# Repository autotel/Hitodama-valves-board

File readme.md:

# to fix:
* ---Teensy-board, connect VCC to teensy 3v---
* ---caps wrong way around in valves boards.---
* ---check about the twistedness of the ribbon cable---

* Cannot use the DAC pins (A21,A22) as digital!

board to control two valves and two pressure sensors from microcontroller.

Electronic design: Avner Peled & Joaquín Aldunate

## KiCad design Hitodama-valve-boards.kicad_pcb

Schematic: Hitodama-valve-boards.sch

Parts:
C1, C2: 100uF 25v; CP_Radial_D8.0mm_P3.80mm
D1, D2: D; D_5W_P12.70mm_Horizontal
H1, H2, H3, H4: MountingHole; MountingHole_3.2mm_M3
J1: Solenoid A; TerminalBlock_Altech_AK300-2_P5.00mm
J2: Solenoid B; TerminalBlock_Altech_AK300-2_P5.00mm
JP1, JP2: (A,B)IN 1; PinHeader_1x02_P2.54mm_Vertical
R1, R5: 80K; R_Axial_DIN0309_L9.0mm_D3.2mm_P12.70mm_Horizontal
R2, R6: 10K; R_Axial_DIN0309_L9.0mm_D3.2mm_P12.70mm_Horizontal
R3, R7: 3.3K; R_Axial_DIN0309_L9.0mm_D3.2mm_P12.70mm_Horizontal
R4, R8: 33K; R_Axial_DIN0309_L9.0mm_D3.2mm_P12.70mm_Horizontal
U1: LM358; DIP-8_W7.62mm_Socket_LongPads
U2: Pressure_b; DIP-6_W10.16mm
U3: Pressure_a; DIP-6_W10.16mm
U4: ChamberBoard_Holder; chamber_board_holder_ 5-5530843-3_male
U5: Pololu-713; pololu713

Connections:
+12V: U4.7, U5.7
/A.IN.1: JP1.1, U4.3, U5.14
/A.IN.2: U4.4, U5.15
/A.PRESSURE: R8.1, U1.1, U4.10
/A.PWM: JP2.2, U4.1, U5.16
/B.IN.1: JP1.2, U4.5, U5.12
/B.IN.2: U4.6, U5.11
/B.PRESSURE: R4.1, U1.7, U4.11
/B.PWM: JP2.1, U4.2, U5.10
/HVA+: D1.1 (K), J1.2, U5.3
/HVA-: D1.2 (A), J1.1, U5.4
/HVB+: D2.1 (K), J2.2, U5.6
/HVB-: D2.2 (A), J2.1, U5.5
/stby: U4.12, U5.13
GND: C1.2, C2.2, R1.1, R5.1, U1.4 (V-), U2.2, U3.2, U4.8, U5.1, U5.9
unnamed: R1.2, R2.2, U1.5 (+)
unnamed: R2.1, U2.4
unnamed: R3.1, R4.2, U1.6 (-)
unnamed: R3.2, U2.1, U2.6
unnamed: R5.2, R6.2, U1.3 (+)
unnamed: R6.1, U3.4
unnamed: R7.1, R8.2, U1.2 (-)
unnamed: R7.2, U3.1, U3.6
VCC: C1.1, C2.1, U1.8 (V+), U2.5, U3.5, U4.9, U5.2

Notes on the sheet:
Modular
Head

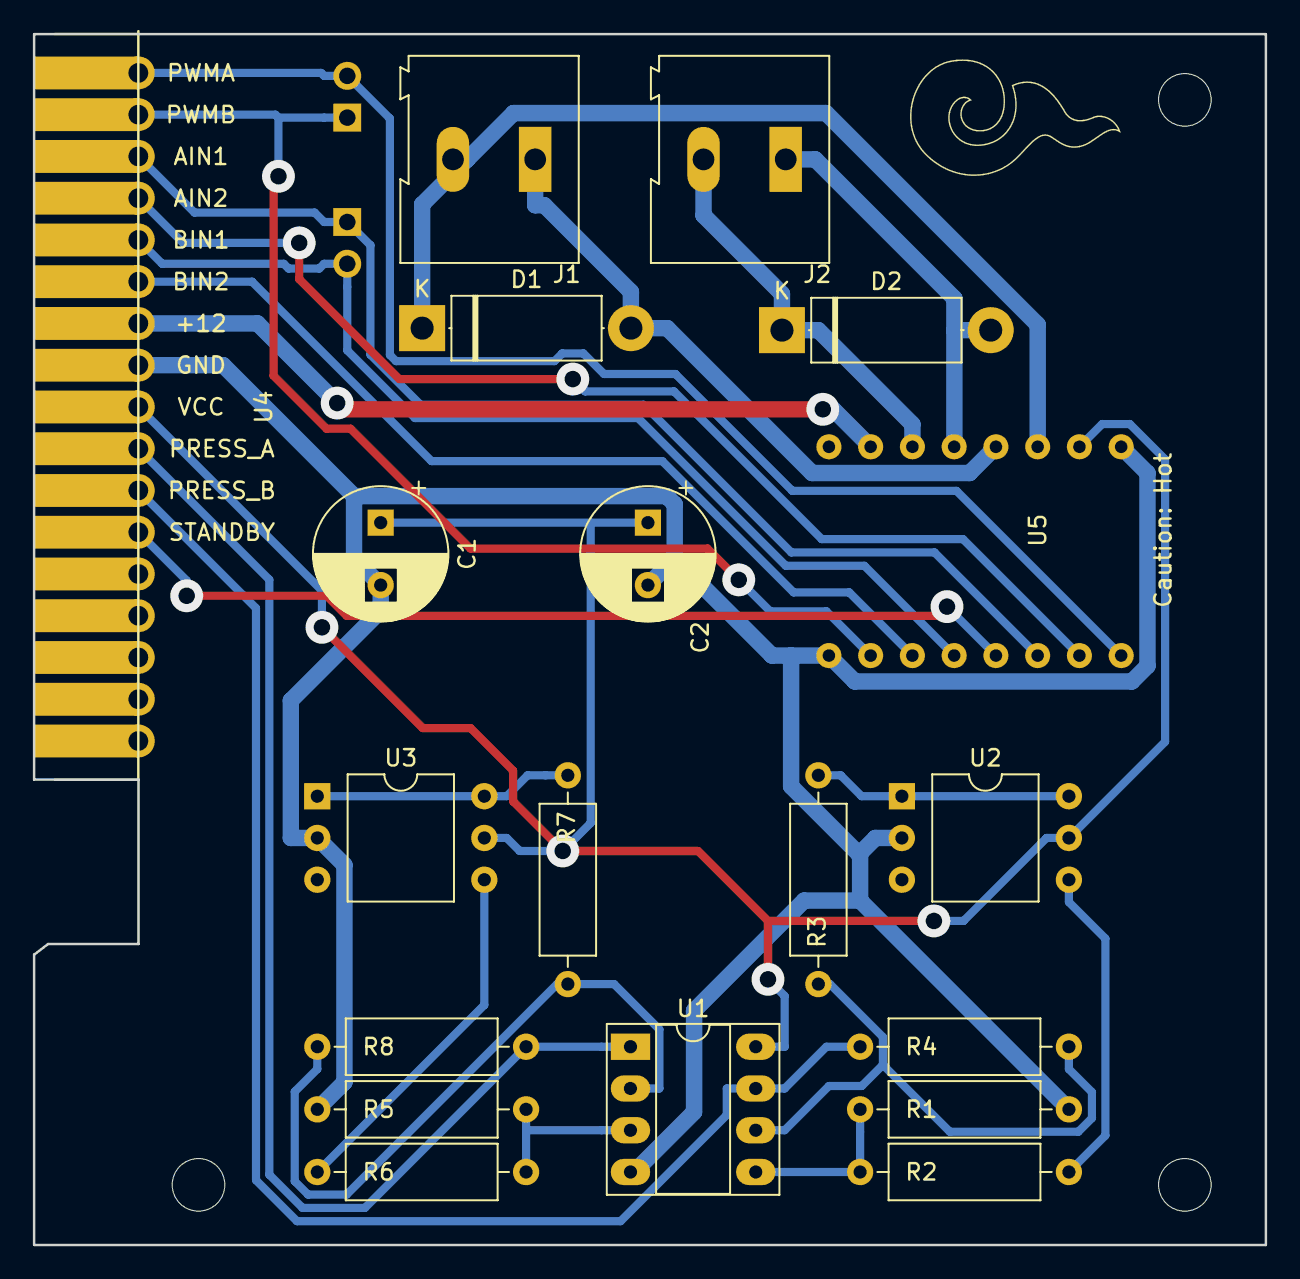
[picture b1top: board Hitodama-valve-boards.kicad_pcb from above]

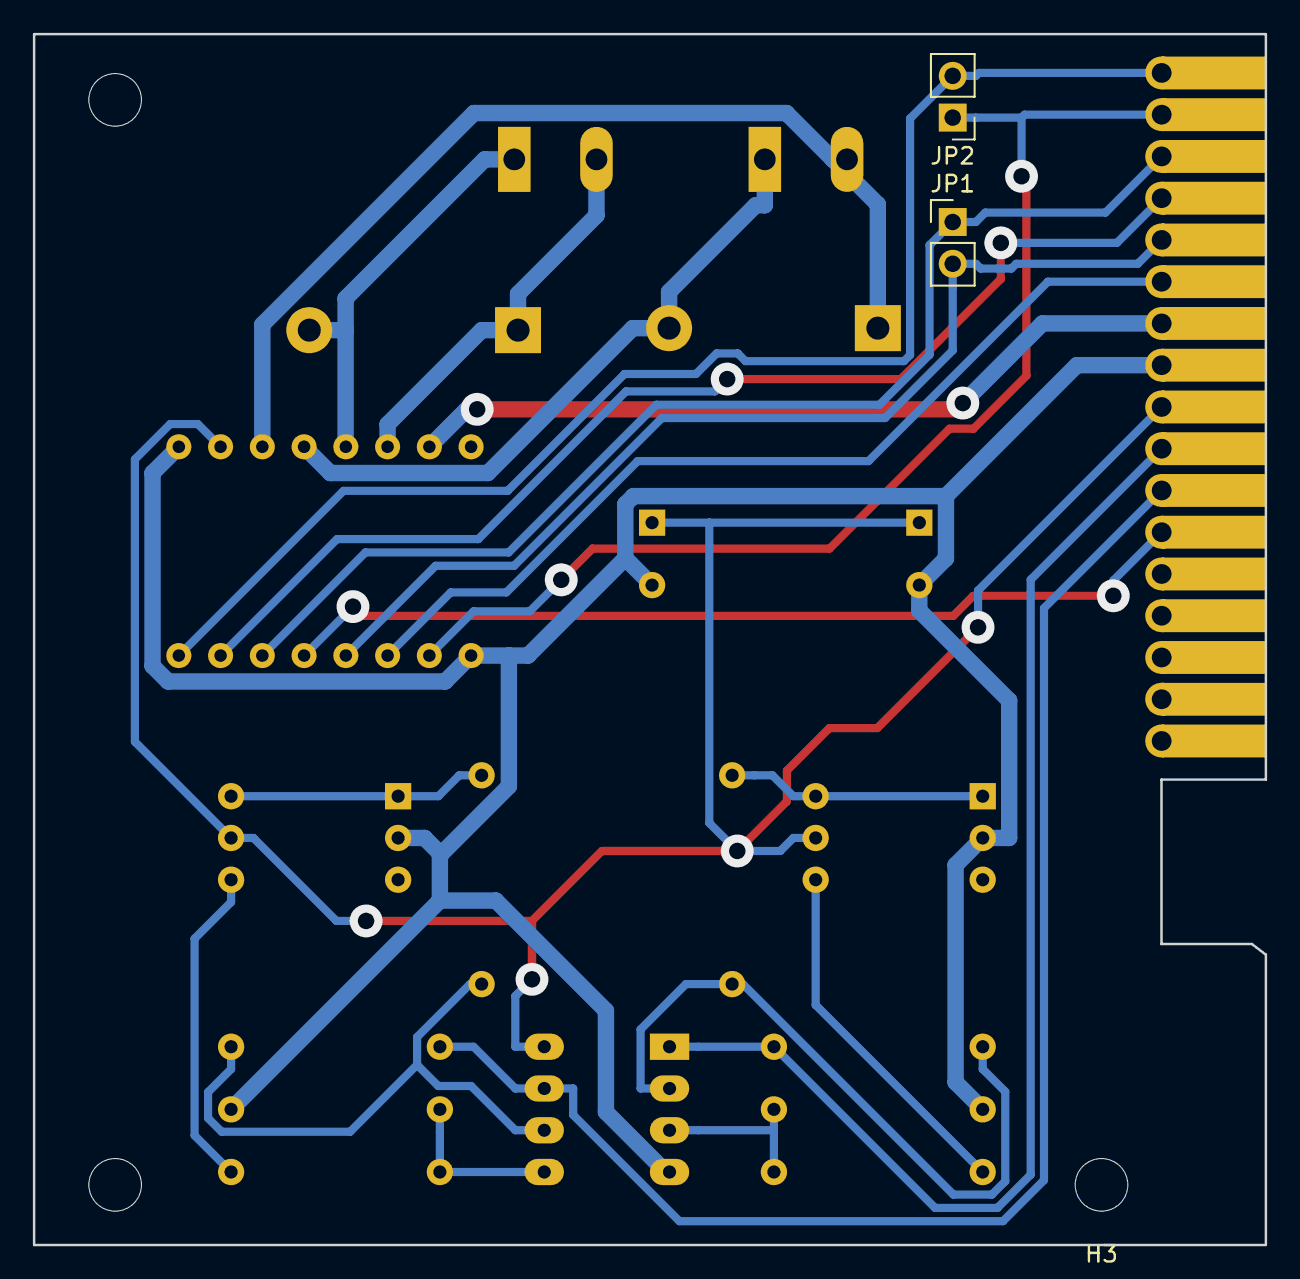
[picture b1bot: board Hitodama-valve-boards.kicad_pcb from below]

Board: 2 copper layers, 74.9 x 73.7 mm, 24 parts (4 on the bottom side), 24 nets.

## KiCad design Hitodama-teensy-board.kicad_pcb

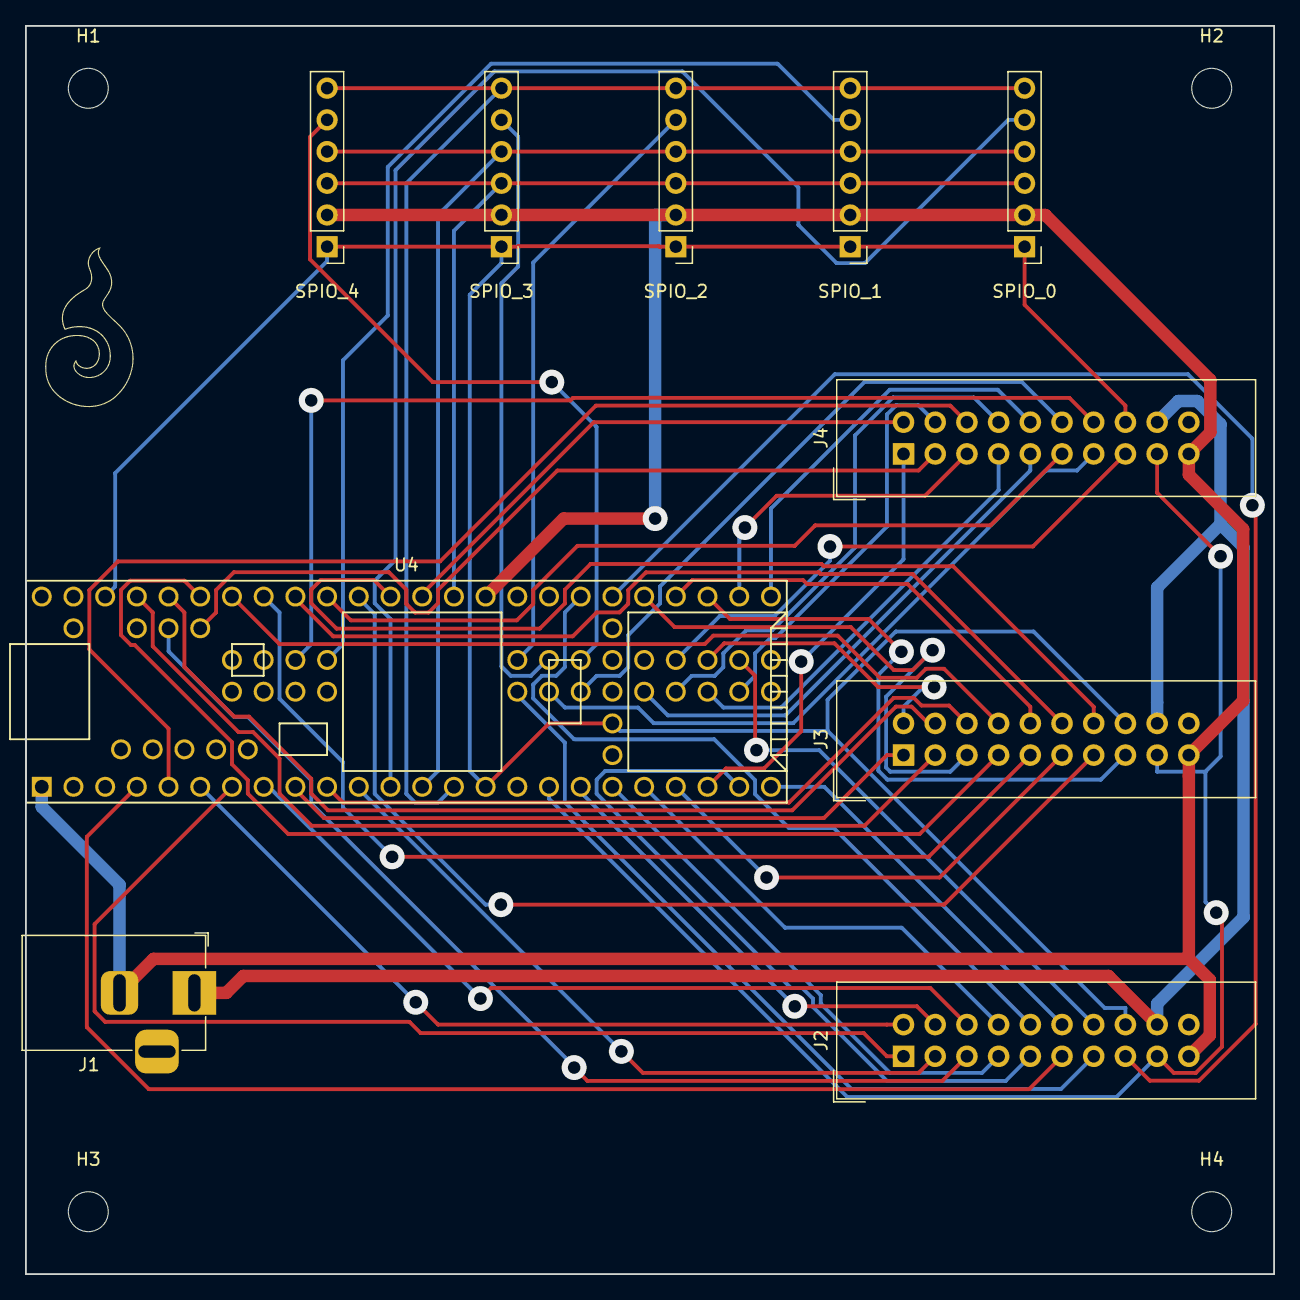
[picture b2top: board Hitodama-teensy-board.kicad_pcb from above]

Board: 2 copper layers, 100.0 x 100.0 mm, 14 parts (0 on the bottom side), 57 nets.

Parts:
H1, H2, H3, H4: MountingHole; MountingHole_3.2mm_M3
J1: Jack-DC; BarrelJack_Horizontal
J2, J3, J4: Conn_01x20_Female; IDC-Header_2x10_P2.54mm_Vertical
SPIO_0, SPIO_1, SPIO_2, SPIO_3, SPIO_4: Conn_01x06_Female; PinHeader_1x06_P2.54mm_Vertical
U4: Teensy3.6; Teensy35_36

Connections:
+12V: J1.1, J2.18, J3.18, J4.18
/All.Stby: J2.17, J3.17, J4.17, U4.17
/ChamberA.ADC: J2.5, U4.56
/ChamberA.D1: J2.2, U4.6
/ChamberA.D2: J2.3, U4.11
/ChamberA.D3: J2.4, U4.18
/ChamberA.PWM: J2.1, U4.7
/ChamberB.ADC: J2.10, U4.36
/ChamberB.D1: J2.7, U4.19
/ChamberB.D2: J2.8, U4.20
/ChamberB.D3: J2.9, U4.23
/ChamberB.PWM: J2.6, U4.8
/ChamberC.ADC: J2.15, U4.35
/ChamberC.D1: J2.12, U4.24
/ChamberC.D2: J2.13, U4.67
/ChamberC.D3: J2.14, U4.76
/ChamberC.PWM: J2.11, U4.4
/ChamberD.ADC: J3.5, U4.34
/ChamberD.D1: J3.2, U4.77
/ChamberD.D2: J3.3, U4.50
/ChamberD.D3: J3.4, U4.49
/ChamberD.PWM: J3.1, U4.9
/ChamberE.ADC: J3.10, U4.33
/ChamberE.D1: J3.7, U4.48
/ChamberE.D2: J3.8, U4.47
/ChamberE.D3: J3.9, U4.46
/ChamberE.PWM: J3.6, U4.10
/ChamberF.ADC: J3.15, U4.32
/ChamberF.D1: J3.12, U4.45
/ChamberF.D2: J3.13, U4.43
/ChamberF.D3: J3.14, U4.42
/ChamberF.PWM: J3.11, U4.21
/ChamberG.ADC: J4.5, U4.31
/ChamberG.D1: J4.2, U4.41
/ChamberG.D2: J4.3, U4.57
/ChamberG.D3: J4.4, U4.73
/ChamberG.PWM: J4.1, U4.22
/ChamberH.ADC: J4.10, U4.30
/ChamberH.D1: J4.7, U4.72
/ChamberH.D2: J4.8, U4.71
/ChamberH.D3: J4.9, U4.70
/ChamberH.PWM: J4.6, U4.5
/ChamberI.ADC: J4.15, U4.78
/ChamberI.D1: J4.12, U4.69
/ChamberI.D2: J4.13, U4.68
/ChamberI.D3: J4.14, U4.84
/ChamberI.PWM: J4.11, U4.44
/SPI0.CS0: SPIO_0.5, U4.12
/SPI0.CS1: SPIO_1.5, U4.83
/SPI0.CS2: SPIO_2.5, U4.82
/SPI0.CS3: SPIO_3.5, U4.81
/SPI0.CS4: SPIO_4.5, U4.80
/SPI0.MISO: SPIO_0.6, SPIO_1.6, SPIO_2.6, SPIO_3.6, SPIO_4.6, U4.14
/SPI0.MOSI: SPIO_0.4, SPIO_1.4, SPIO_2.4, SPIO_3.4, SPIO_4.4, U4.13
/SPI0.SCK: SPIO_0.3, SPIO_1.3, SPIO_2.3, SPIO_3.3, SPIO_4.3, U4.40
GND: J1.2, J2.19, J3.19, J4.19, SPIO_0.2, SPIO_1.2, SPIO_2.2, SPIO_3.2, SPIO_4.2, U4.1, U4.39
VCC: J2.16, J3.16, J4.16, SPIO_0.1, SPIO_1.1, SPIO_2.1, SPIO_3.1, SPIO_4.1, U4.15, U4.26, U4.51

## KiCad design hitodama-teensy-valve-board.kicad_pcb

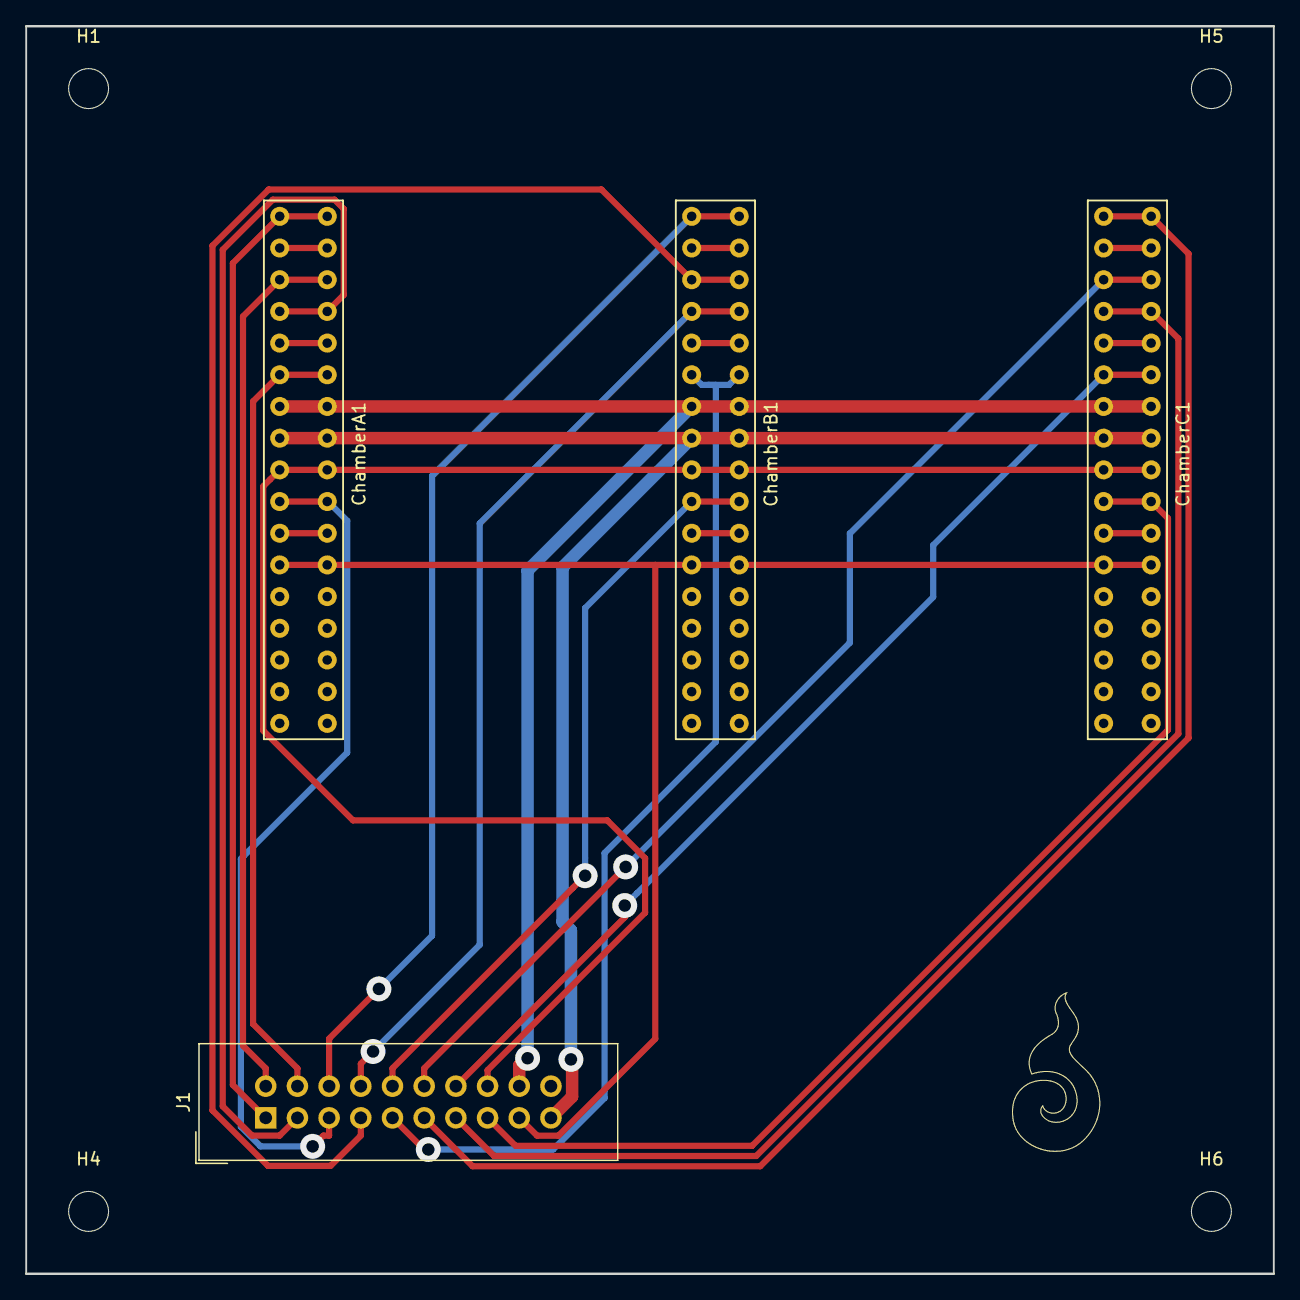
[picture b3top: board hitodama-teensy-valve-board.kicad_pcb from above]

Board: 2 copper layers, 100.0 x 100.0 mm, 8 parts (0 on the bottom side), 19 nets.

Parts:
ChamberA1: ChamberBoard_Holder; 5-5530843-3 female
ChamberB1: ChamberBoard_Holder; 5-5530843-3 female
ChamberC1: ChamberBoard_Holder; 5-5530843-3 female
H1, H4, H5, H6: MountingHole; MountingHole_3.2mm_M3
J1: Conn_01x20_Female; IDC-Header_2x10_P2.54mm_Vertical

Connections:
+12V: ChamberA1.7, ChamberB1.7, ChamberC1.7, J1.18
/All.Stby: ChamberA1.12, ChamberB1.12, ChamberC1.12, J1.17
/ChamberA.ADC: ChamberA1.10, J1.5
/ChamberA.D1: ChamberA1.3, J1.2
/ChamberA.D2: ChamberA1.4, J1.3
/ChamberA.D3: ChamberA1.6, J1.4
/ChamberA.PWM: ChamberA1.1, J1.1
/ChamberB.ADC: ChamberB1.10, J1.10
/ChamberB.D1: ChamberB1.3, J1.7
/ChamberB.D2: ChamberB1.4, J1.8
/ChamberB.D3: ChamberB1.6, J1.9
/ChamberB.PWM: ChamberB1.1, J1.6
/ChamberC.ADC: ChamberC1.10, J1.15
/ChamberC.D1: ChamberC1.3, J1.12
/ChamberC.D2: ChamberC1.4, J1.13
/ChamberC.D3: ChamberC1.6, J1.14
/ChamberC.PWM: ChamberC1.1, J1.11
GND: ChamberA1.8, ChamberB1.8, ChamberC1.8, J1.19
VCC: ChamberA1.9, ChamberB1.9, ChamberC1.9, J1.16

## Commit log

2019-04-16 initial, demo board for chamber controller
2019-04-16 fixed capacitor colliding motor driver board
2019-04-16 picture and readme
2019-04-16 picture link raw
2019-04-16 improved adding +12v connector
2019-04-17 Change track definitions to fit Fablab's
2019-04-17 changed design rules for milling machine and consequently re-routed everyhting
2019-04-23 Separate the two board into different sch files. Added missing jumper (SCH only) and missing Vias for a jumber
2019-04-23 Label all valve&motor controlle pins @ teensy
2019-04-23 Coordinate Connectors on both boards
2019-04-23 (auto) routing
2019-04-25 push some paths around
2019-04-26 schematic add SPI ports & 12 v power connector
2019-04-26 route & DRC teensy board
2019-04-30 separated the teensy board into four modules, so that it fits in smaller PCB's. Improved the chamber board, and added rules so that auto-router can figure out the optimal 1 layer+jumpers route
2019-05-02 teensy board change 21 pins headers into 20 pins headers.
2019-05-03 fixed forgotten swap of pin headers on teensy-valves-board bridge
2019-05-13 2 row connector, routed on intermediate board
2019-05-14 even greater trace widths
2019-05-20 fix misaligned hole
2019-05-21 trying different routing options teensy board
2019-05-30 fix some mistakes
2019-05-30 Added HITODAMA logo footprint
2019-05-31 remove useless texts
2019-05-31 generate seedstudio gerber files
2019-06-01 Vertical hitodama logo
2019-06-02 fix cap wrong orientation & teensy vcc.
2019-06-02 reduce teensy board size to 100x100
2019-06-02 change connectors into edge connector 5-5530843-3, TE Connectivity
2019-06-02 fix wrong adc pins in teensy board
2019-06-02 added logos
2019-06-02 Merge branch 'joaquin' into HEAD
    # Conflicts:
    # Hitodama-teensy-board.kicad_pcb
2019-06-02 check merge
2019-06-02 enable silkscreen teensy board
2019-08-18 update pic. & fix cutout not being exactly closed.
